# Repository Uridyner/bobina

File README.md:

# Bobina/Bob 3.0
Holis a todos, estos son los códigos de Bobina (también conocida como Bob 3.0)

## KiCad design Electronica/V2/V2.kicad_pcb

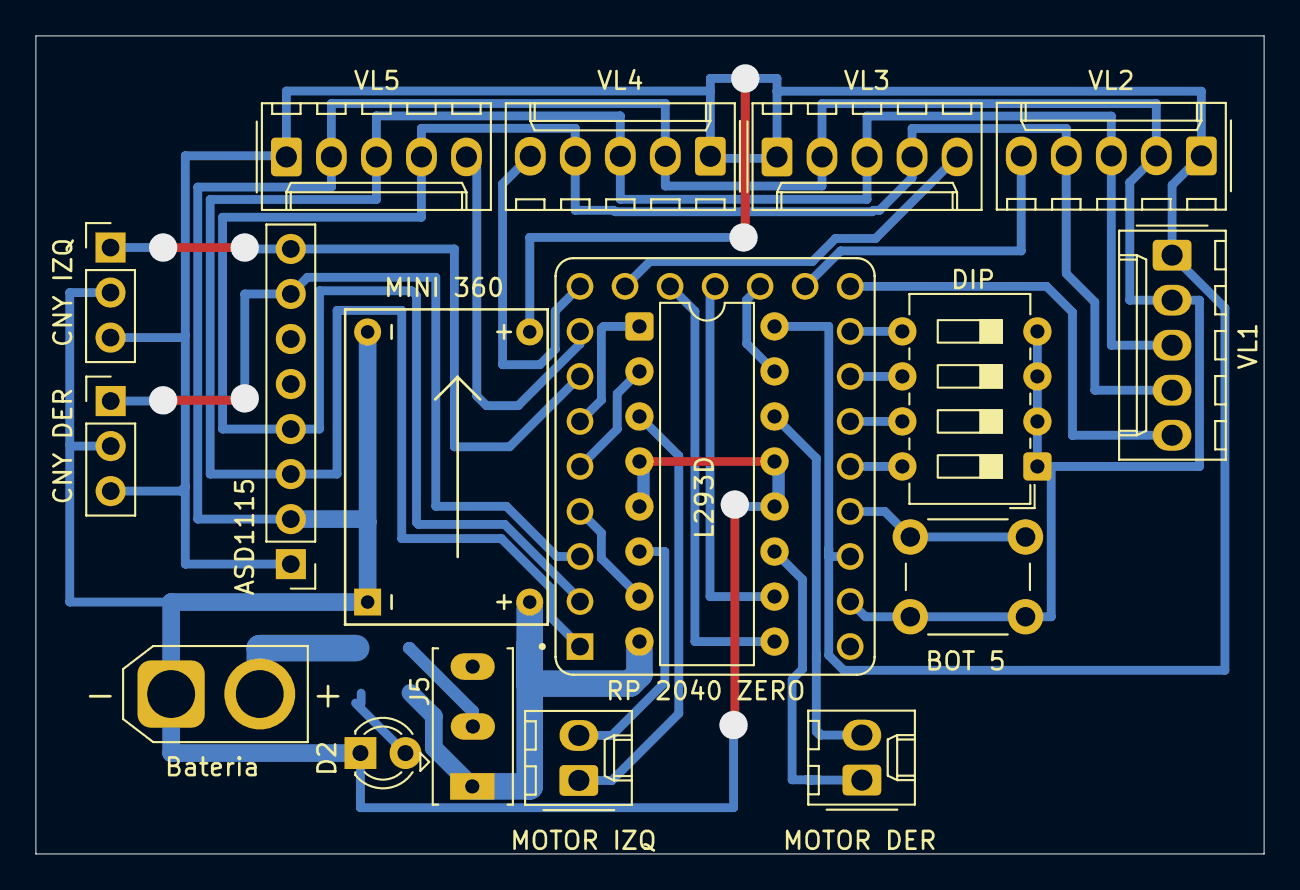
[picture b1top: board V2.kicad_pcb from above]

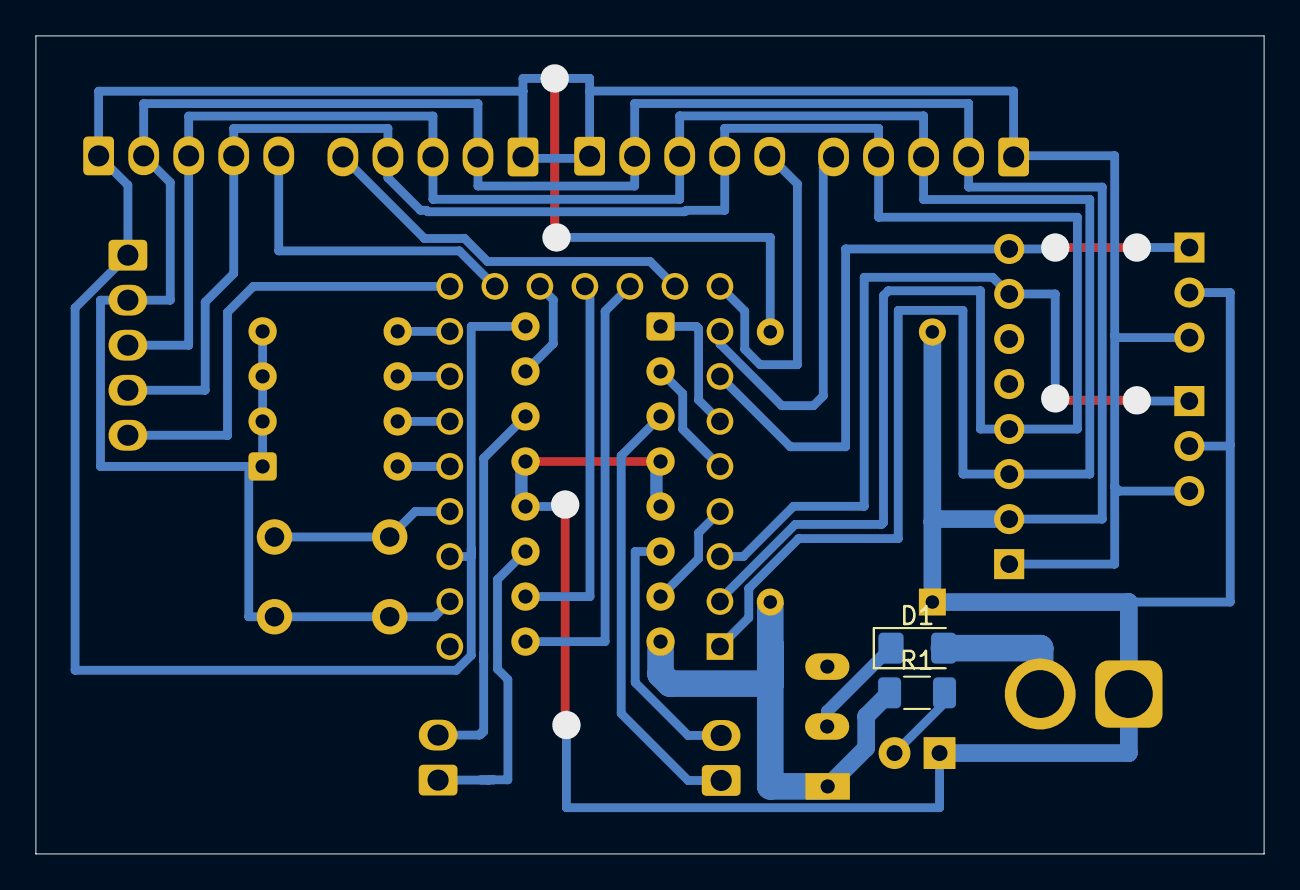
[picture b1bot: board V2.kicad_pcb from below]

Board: 2 copper layers, 69.3 x 46.2 mm, 20 parts (2 on the bottom side), 30 nets.

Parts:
ASD1115: Conn_01x08_Pin; PinHeader_1x08_P2.54mm_Vertical
BOT 5: SW_Push; SW_PUSH_6mm
Bateria: Power Input 1; AMASS_XT30U-F_1x02_P5.0mm_Vertical
CNY DER: Conn_01x03_Pin; PinHeader_1x03_P2.54mm_Vertical
CNY IZQ: Conn_01x03_Pin; PinHeader_1x03_P2.54mm_Vertical
D1: 1N4007; D_1206_3216Metric_Pad1.42x1.75mm_HandSolder
D2: LED; LED_D3.0mm_FlatTop
DIP: SW_DIP_x04; SW_DIP_SPSTx04_Slide_6.7x11.72mm_W7.62mm_P2.54mm_LowProfile
J5: On/Off General; SW_Slide_SPDT_Straight_CK_OS102011MS2Q
L293D: L293D; DIP-16_W7.62mm
MINI 360: Mini360_Module
MOTOR DER: Conn_01x02_Socket; Molex_KK-254_AE-6410-02A_1x02_P2.54mm_Vertical
MOTOR IZQ: Conn_01x02_Socket; Molex_KK-254_AE-6410-02A_1x02_P2.54mm_Vertical
R1: 220; R_1206_3216Metric_Pad1.30x1.75mm_HandSolder
RP 2040 ZERO: RP2040-ZERO; MODULE_RP2040-ZERO
VL1, VL2, VL3, VL4, VL5: Conn_01x05_Pin; Molex_KK-254_AE-6410-05A_1x05_P2.54mm_Vertical

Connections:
+3.3V: ASD1115.1, CNY DER.3, CNY IZQ.3, L293D.16 (VCC1), MINI 360.3 (OUT+), RP 2040 ZERO.21 (3V3), VL1.1, VL2.1, VL3.1, VL4.1, VL5.1
+12V: J5.1 (A), L293D.8 (VCC2), MINI 360.1 (IN+), R1.1
BOT1: DIP.8, RP 2040 ZERO.19 (GP28)
BOT2: DIP.7, RP 2040 ZERO.18 (GP27)
BOT3: DIP.6, RP 2040 ZERO.17 (GP26)
BOT4: DIP.5, RP 2040 ZERO.16 (GP15)
BOT5: BOT 5.2, RP 2040 ZERO.20 (GP29)
CNY_DER: ASD1115.7, CNY DER.1, RP 2040 ZERO.3 (GP2)
CNY_IZQ: ASD1115.8, CNY IZQ.1, RP 2040 ZERO.7 (GP6)
GND: ASD1115.2, BOT 5.1, Bateria.1, CNY DER.2, CNY IZQ.2, D2.1 (K), DIP.1, DIP.2, DIP.3, DIP.4, L293D.4 (GND), L293D.5 (GND), L293D.12 (GND), L293D.13 (GND), MINI 360.2 (IN-), MINI 360.4 (OUT-), RP 2040 ZERO.22 (GND), VL1.2, VL2.2, VL3.2, VL4.2, VL5.2
MOTORA1: L293D.2 (1A), RP 2040 ZERO.5 (GP4)
MOTORA2: L293D.7 (2A), RP 2040 ZERO.4 (GP3)
MOTORB1: L293D.10 (3A), RP 2040 ZERO.12 (GP11)
MOTORB2: L293D.15 (4A), RP 2040 ZERO.13 (GP12)
unnamed: Bateria.2, D1.2 (A)
unnamed: D1.1 (K), J5.2 (B)
unnamed: D2.2 (A), R1.2
unnamed: L293D.11 (3Y), MOTOR DER.1
unnamed: L293D.14 (4Y), MOTOR DER.2
unnamed: L293D.3 (1Y), MOTOR IZQ.1
unnamed: L293D.6 (2Y), MOTOR IZQ.2
PWMA: L293D.1 (EN1,2), RP 2040 ZERO.6 (GP5)
PWMB: L293D.9 (EN3,4), RP 2040 ZERO.11 (GP10)
SCL: ASD1115.3, RP 2040 ZERO.1 (GP0), VL1.3, VL2.3, VL3.3, VL4.3, VL5.3
SDA: ASD1115.4, RP 2040 ZERO.2 (GP1), VL1.4, VL2.4, VL3.4, VL4.4, VL5.4
VL1: RP 2040 ZERO.15 (GP14), VL1.5
VL2: RP 2040 ZERO.14 (GP13), VL2.5
VL3: RP 2040 ZERO.10 (GP9), VL3.5
VL4: RP 2040 ZERO.9 (GP8), VL4.5
VL5: RP 2040 ZERO.8 (GP7), VL5.5

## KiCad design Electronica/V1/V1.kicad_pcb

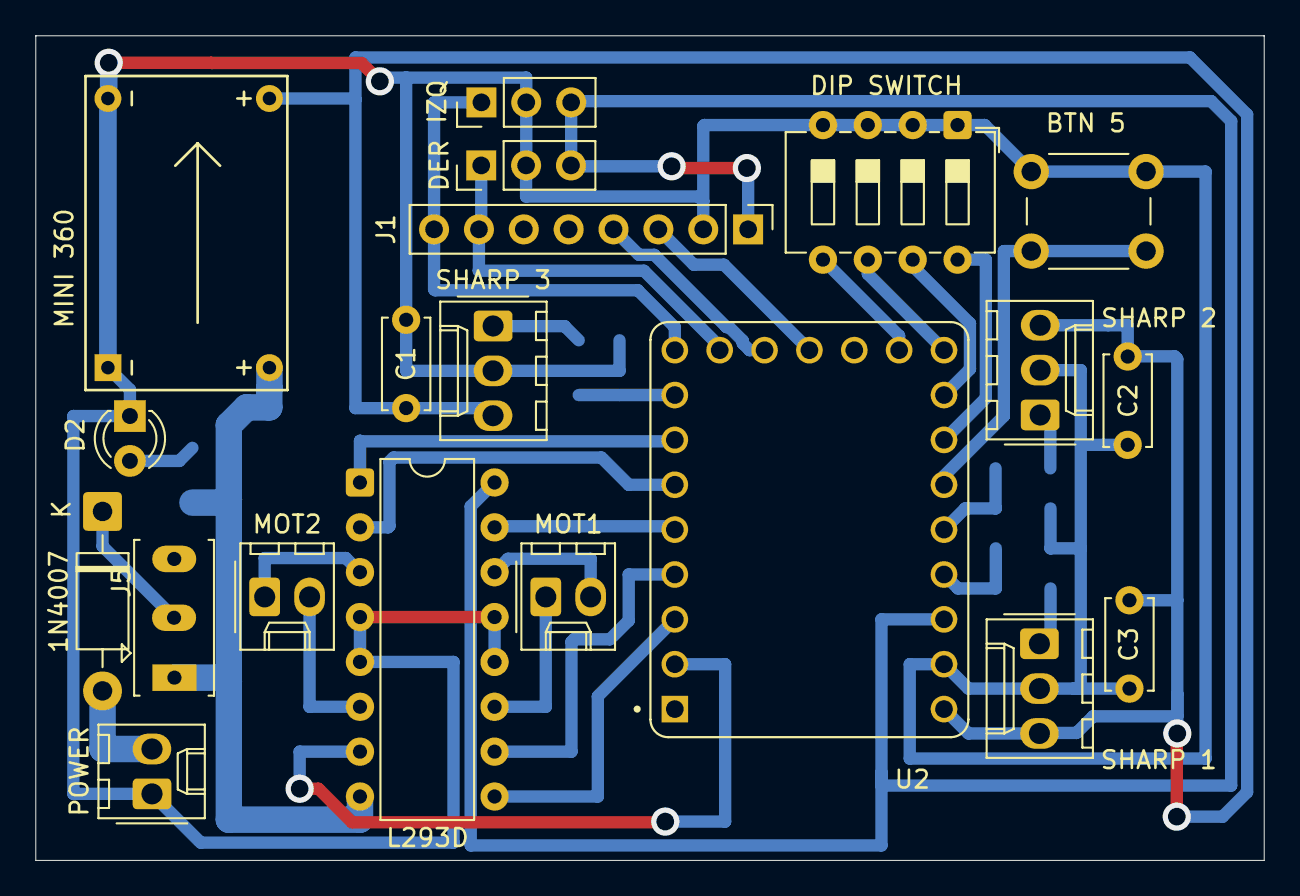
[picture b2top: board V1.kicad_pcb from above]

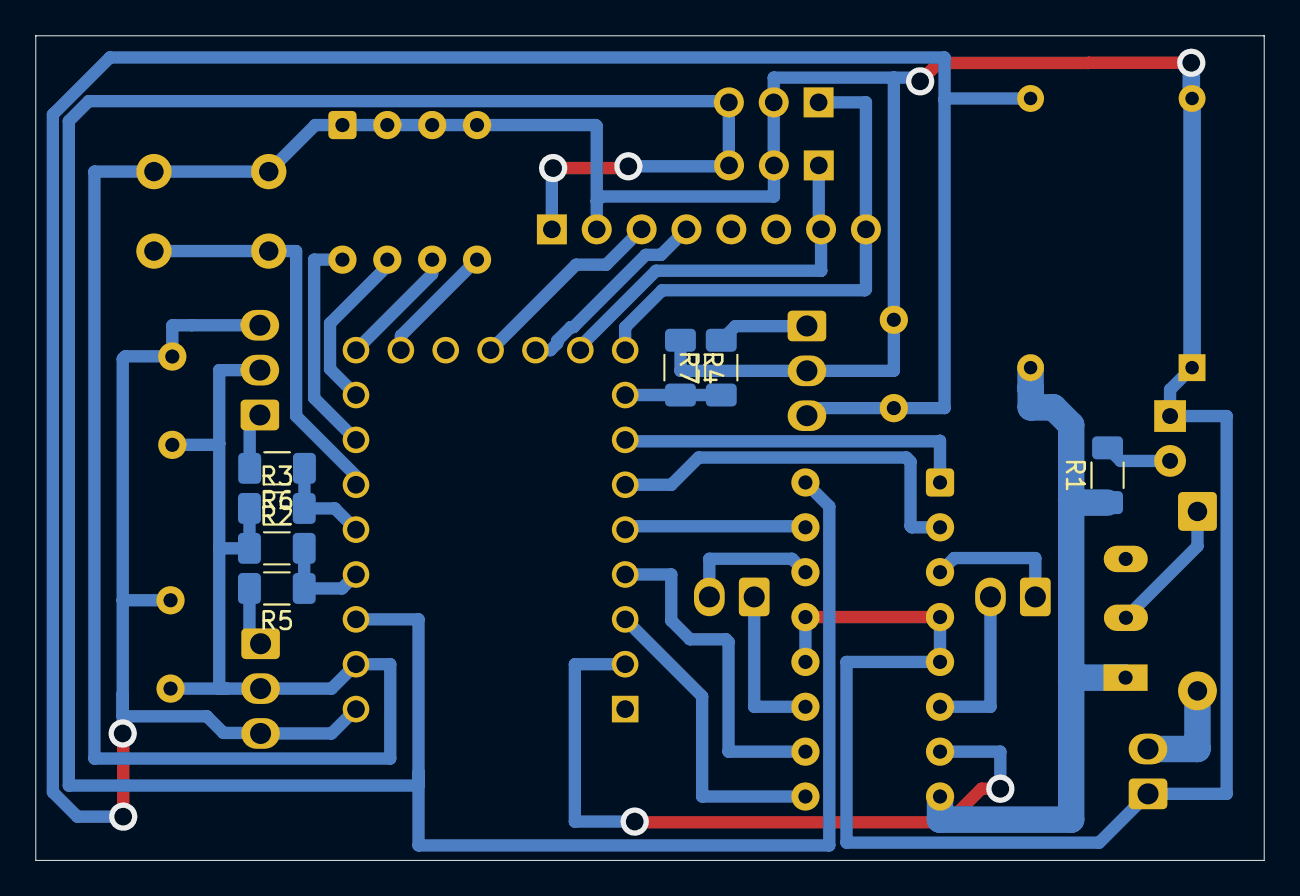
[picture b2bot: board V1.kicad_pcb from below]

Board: 2 copper layers, 69.6 x 46.7 mm, 27 parts (7 on the bottom side), 32 nets.

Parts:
1N4007: 1N4007; D_DO-41_SOD81_P10.16mm_Horizontal
BTN 5: SW_Push; SW_PUSH_6mm
C1, C2, C3: C_Small; C_Disc_D5.0mm_W2.5mm_P5.00mm
D2: LED; LED_D3.0mm_FlatTop
DER: Conn_01x03_Pin; PinHeader_1x03_P2.54mm_Vertical
DIP SWITCH: SW_DIP_x04; SW_DIP_SPSTx04_Slide_6.7x11.72mm_W7.62mm_P2.54mm_LowProfile
IZQ: Conn_01x03_Pin; PinHeader_1x03_P2.54mm_Vertical
J1: Conn_01x08_Pin; PinHeader_1x08_P2.54mm_Vertical
J5: On/Off General; SW_Slide_SPDT_Straight_CK_OS102011MS2Q
L293D: L293D; DIP-16_W7.62mm
MINI 360: Mini360_Module
MOT1, MOT2: Conn_01x02_Socket; Molex_KK-254_AE-6410-02A_1x02_P2.54mm_Vertical
POWER: Power Input 1; Molex_KK-254_AE-6410-02A_1x02_P2.54mm_Vertical
R1: 220; R_1206_3216Metric_Pad1.30x1.75mm_HandSolder
R2, R3, R4, R5, R6, R7: R; R_1206_3216Metric_Pad1.30x1.75mm_HandSolder
SHARP 1, SHARP 2, SHARP 3: Conn_01x03_Pin; Molex_KK-254_AE-6410-03A_1x03_P2.54mm_Vertical
U2: RP2040-ZERO; MODULE_RP2040-ZERO

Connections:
+3.3V: DER.3, IZQ.3, J1.1, L293D.16 (VCC1), U2.21 (3V3)
+5V: C1.2, C2.2, C3.2, MINI 360.3 (OUT+), SHARP 1.3, SHARP 2.3, SHARP 3.3, U2.23 (5V)
+12V: J5.1 (A), L293D.8 (VCC2), MINI 360.1 (IN+), R1.1
BOT1: DIP SWITCH.8, U2.17 (GP26)
BOT2: DIP SWITCH.7, U2.16 (GP15)
BOT3: DIP SWITCH.6, U2.15 (GP14)
BOT4: DIP SWITCH.5, U2.14 (GP13)
BOT5: BTN 5.2, U2.18 (GP27)
CNY_DER: DER.1, J1.7, U2.10 (GP9)
CNY_IZQ: IZQ.1, J1.8, U2.9 (GP8)
GND: BTN 5.1, C1.1, C2.1, C3.1, D2.1 (K), DER.2, DIP SWITCH.1, DIP SWITCH.2, DIP SWITCH.3, DIP SWITCH.4, IZQ.2, J1.2, L293D.4 (GND), L293D.5 (GND), L293D.12 (GND), L293D.13 (GND), MINI 360.2 (IN-), MINI 360.4 (OUT-), POWER.1, R2.1, R3.1, R4.1, SHARP 1.2, SHARP 2.2, SHARP 3.2, U2.22 (GND)
MOTORA1: L293D.2 (1A), U2.6 (GP5)
MOTORA2: L293D.7 (2A), U2.2 (GP1)
MOTORB1: L293D.10 (3A), U2.4 (GP3)
MOTORB2: L293D.15 (4A), U2.5 (GP4)
unnamed: 1N4007.2 (A), POWER.2
unnamed: 1N4007.1 (K), J5.2 (B)
unnamed: D2.2 (A), R1.2
unnamed: L293D.11 (3Y), MOT1.1
unnamed: L293D.14 (4Y), MOT1.2
unnamed: L293D.3 (1Y), MOT2.1
unnamed: L293D.6 (2Y), MOT2.2
PWMA: L293D.1 (EN1,2), U2.7 (GP6)
PWMB: L293D.9 (EN3,4), U2.3 (GP2)
Pin_Sharp_1: R2.2, R5.1, U2.20 (GP29)
Pin_Sharp_2: R3.2, R6.1, U2.19 (GP28)
Pin_Sharp_3: R4.2, R7.1, U2.8 (GP7)
SCL: J1.3, U2.12 (GP11)
SDA: J1.4, U2.11 (GP10)
Sharp1: R5.2, SHARP 1.1
Sharp2: R6.2, SHARP 2.1
Sharp3: R7.2, SHARP 3.1

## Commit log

2024-05-31 Add a temporary README
2024-05-31 Agregar el símbolo electrónico del inductor al README
2024-05-31 Whoops!
2024-06-19 Agregar prueba de los sensores
2024-06-19 Arreglar error boludo\ me olvide de cambiar la resolucion del ADC :/
2024-06-19 porque soy tan tonto :(
2024-07-05 Agregar prueba de motores
2024-07-05 Arreglar prueba de sensores
2024-07-06 Prueba motores con pines
2024-07-11 Arreglar archivos subidos incorrectamente
2024-07-11 Arreglar pruebas
2024-07-11 Agregar prueba inicial de motores y sensores
2024-07-11 Renombrar bobina v1 a bobina v0
2024-07-11 Codigo v1!!!!!
2024-07-29 agrego unos codigos simplones
2024-08-01 prueba todo finaaal
2024-08-02 Terminar (por favor) el código de Bobina v1
2024-08-02 ups :P
2024-08-03 FUNCIONAAAAAAAAAAAAAAAAAA ITBA
2024-08-03 Implementar selección de dirección preferida
2024-08-28 ITBA Asimov Cup
2024-09-06 Convertir tiempo que retrocede a una variable, cambiar el método de suavizamiento y hacer que use más lecturas de los sharp
2024-09-07 Arreglar descripciones y comentarios
    De la constexpr TIEMPO_RETROCEDER_MS
2024-09-07 Bajar velocidades máximas
    Las bajé porque si no detectaba al oponente o se caía
2024-09-07 Bajar lecturas de los sharps para el suavizado
    Noté que a veces no detectaba al oponente porque lo veía muy poco tiempo y seguía girando.
    Por eso baje las lecturas de los sharps de 5 a 3.
2024-09-07 Agregar código de avance automático
    Es parecido a lo que hace el mini sumo de Prieto para evitar que se pare la pelea.
    Además le gustó la idea. :smiley:
2024-09-07 Desactivar modo debug
2024-09-07 Cambiar suavizado a usar un promedio
2024-09-07 Cambiar y arreglar tiempos
    Cambié los de retroceso y avance forzado, además de agregar las partes que faltaban
2024-09-07 Cambiar valores para los sharps
    Cambié la distancia de activación, bajé la frecuencia y baje las lecturas utilizadas para el promedio
2024-09-07 Cambiar valores para los CNYs
2024-09-07 Hacer que vaya a velocidad máxima si tiene algo adelante
    ...y no detectó blanco
2024-09-07 Código boludo de laverinto
    No se, lo hice porque estaba aburrido y bueno :P
2024-09-07 Cambiar el orden de los nombres en el README.md
    Bobina es el nombre más usado, así que lo moví para que este primero
2024-09-10 Codigo Laberinto Prueba 2
2024-09-11 LIBRERIA PARA SHARPS!!!!!!
2024-09-11 PRUEBA LEDS
2024-09-12 Agregar delay
2024-09-13 Agregar libreria de SharpIR
2024-09-13 Sacar delay y reducir lecturas por segundo de los sharp
2024-09-14 SON LAS 2 DE LA MAÑANA
2024-09-14 LOS SHARPS AAAAAAAAAAAAAAAAAAAAAAAAAAAAAAAAAAAA LOS SHARP
2024-09-14 Hacer que siga girando en esa dirección cuando ve algo
2024-10-19 Implementar mejor manera de mostrar la estrategia seleccionada
2024-10-19 Vamos bobina!!!!!!!
2024-10-19 Porfis Bobina funcioná te lo ruego}
2024-11-05 Implementar estrategia básica
2024-11-06 Implementar selección de estrategia y arreglar errores de compilación
2024-11-06 Cambiar velocidad de los motores y arreglar advertencia de compilación
2024-11-06 Arreglar constantes
2024-11-06 Cambiar constantes relacionadas a la lectura de sharps
2024-11-06 Cambiar visualización de selección de estrategia
2024-11-06 Agregar avance forzado y que retroceda por menos tiempo si acaba de retroceder
2024-11-09 Competencia final del año!!!
2024-11-09 Bueno, nos llevamos una sorpresa
2025-01-06 Last upload
2025-01-06 Media upload
2025-09-01 PLACA V1
2025-09-02 placa v2
2025-09-02 placa v2 con xt30
